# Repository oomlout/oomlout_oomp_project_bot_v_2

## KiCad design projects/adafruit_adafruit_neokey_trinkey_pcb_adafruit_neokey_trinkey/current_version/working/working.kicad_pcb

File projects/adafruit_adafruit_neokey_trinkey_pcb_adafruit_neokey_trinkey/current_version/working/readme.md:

# adafruit_neokey_trinkey_pcb
 
## summary 
* id: adafruit_adafruit_neokey_trinkey_pcb_adafruit_neokey_trinkey
* user: adafruit
* name: adafruit_neokey_trinkey_pcb
* board: adafruit_neokey_trinkey
* repo: https://github.com/adafruit/Adafruit-NeoKey-Trinkey-PCB

* src_file_repo_sch: 
* src_file_repo_sch_link: https://github.com/adafruit/Adafruit-NeoKey-Trinkey-PCB/tree/main/
* full details link: https://github.com/oomlout/oomlout_oomp_project_bot_v_2/tree/main/projects/adafruit_adafruit_neokey_trinkey_pcb_adafruit_neokey_trinkey/current_version/working  

## schematic  
  
[schematic (pdf)](working_schematic.pdf) 

## pcb  

[board (pdf)](working.pdf)  

## working_bom
| Id | Designator | Footprint | Quantity | Designation | Supplier and ref |  | None | 
| --- | --- | --- | --- | --- | --- | --- | --- | 
| 1 | SWD0 | TP15R | 1 | SWD |  |  | [''] | 
| 2 | RESET0 | BTN_KMR2_4.6X2.8 | 1 | KMR2 |  |  | [''] | 
| 3 | U$8 | PCBFEAT-REV-040 | 1 |  |  |  | [''] | 
| 4 | SWC0 | TP15R | 1 | SWC |  |  | [''] | 
| 5 | C8,C3 | 0805-NO | 2 | 10uF |  |  | [''] | 
| 6 | FID2,FID1 | FIDUCIAL_1MM | 2 | FIDUCIAL_1MM |  |  | [''] | 
| 7 | C4,C5 | 0603-NO | 2 | 1uF |  |  | [''] | 
| 8 | IC3 | QFN32_5MM | 1 | ATSAMD21E |  |  | [''] | 
| 9 | U$6 | ADAFRUIT_9MM | 1 |  |  |  | [''] | 
| 10 | RST0 | TP16R | 1 | RST |  |  | [''] | 
| 11 | U1 | SOT23-5 | 1 | AP2112K-3.3 |  |  | [''] | 
| 12 | SW1 | KAILH_BOX_MX_NOSTABILIZERS | 1 | MX |  |  | [''] | 
| 13 | CN1 | USBA_PCB | 1 |  |  |  | [''] | 
| 14 | LED1 | NEO3535_REVERSE | 1 | WS2812B_SK6812E |  |  | [''] | 

## bom_schematic
| Ref | Qnty | Value | Cmp name | Footprint | Description | Vendor | DNP | 
| --- | --- | --- | --- | --- | --- | --- | --- | 
| C3, C8 | 2 | 10uF | CAP_CERAMIC0805-NOOUTLINE | working:0805-NO |  |  |  | 
| C4, C5 | 2 | 1uF | CAP_CERAMIC0603_NO | working:0603-NO |  |  |  | 
| CN1 | 1 | USB_TYPEAPCB | USB_TYPEAPCB | working:USBA_PCB |  |  |  | 
| FID1, FID2 | 2 | FIDUCIAL_1MM | FIDUCIAL_1MM | working:FIDUCIAL_1MM |  |  |  | 
| IC3 | 1 | ATSAMD21E | ATSAMD21E | working:QFN32_5MM |  |  |  | 
| LED1 | 1 | WS2812B_SK6812E | WS2812B_SK6812E | working:NEO3535_REVERSE |  |  |  | 
| RESET0 | 1 | KMR2 | SWITCH_TACT_SMT4.6X2.8 | working:BTN_KMR2_4.6X2.8 |  |  |  | 
| RST0 | 1 | TPTP16R | TPTP16R | working:TP16R |  |  |  | 
| SW1 | 1 | MX | SWITCH_PUSHBUTTON_KAILH_THMSIMPLE | working:KAILH_BOX_MX_NOSTABILIZERS |  |  |  | 
| SWC0 | 1 | TPTP15R | TPTP15R | working:TP15R |  |  |  | 
| SWD0 | 1 | TPTP15R | TPTP15R | working:TP15R |  |  |  | 
| U1 | 1 | AP2112K-3.3 | VREG_SOT23-5 | working:SOT23-5 |  |  |  |

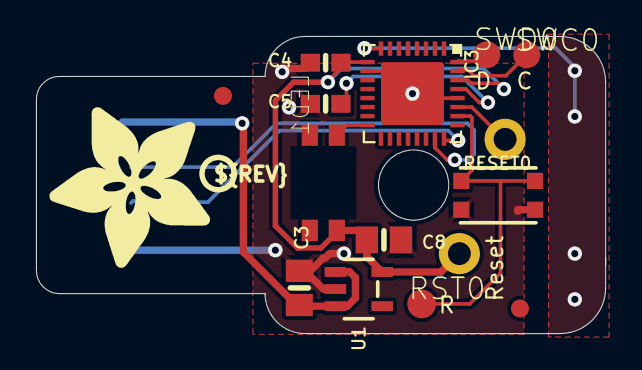
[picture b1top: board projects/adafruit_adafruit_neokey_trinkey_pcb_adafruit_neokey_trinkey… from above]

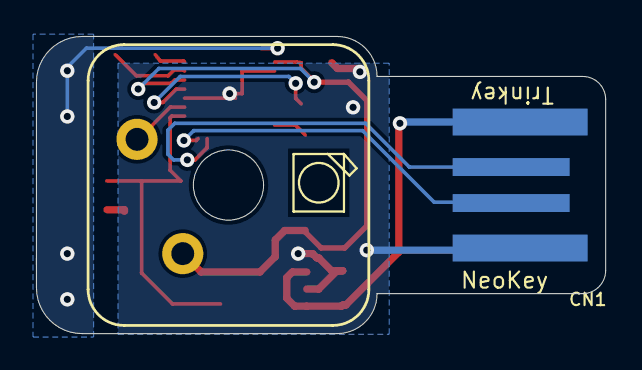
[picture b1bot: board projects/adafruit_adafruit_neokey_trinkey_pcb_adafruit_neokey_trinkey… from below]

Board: 2 copper layers, 31.6 x 16.5 mm, 17 parts (3 on the bottom side), 11 nets.

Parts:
C3, C8: 10uF; 0805-NO
C4, C5: 1uF; 0603-NO
CN1: USBA_PCB
FID1, FID2: FIDUCIAL_1MM
IC3: ATSAMD21E; QFN32_5MM
LED1: WS2812B_SK6812E; NEO3535_REVERSE
RESET0: KMR2; BTN_KMR2_4.6X2.8
RST0: RST; TP16R
SW1: MX; KAILH_BOX_MX_NOSTABILIZERS
SWC0: SWC; TP15R
SWD0: SWD; TP15R
U1: AP2112K-3.3; SOT23-5
U$6: ADAFRUIT_9MM
U$8: PCBFEAT-REV-040

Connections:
3.3V: C4.1, C8.1, IC3.9, IC3.30, LED1.1-VDD, SW1.1, U1.5
D+: CN1.USB_PLUS, IC3.24
D-: CN1.USB_NEG, IC3.23
GND: C3.2, C4.2, C5.2, C8.2, CN1.GND, IC3.10, IC3.28, IC3.33, LED1.3-GND, RESET0.B, RESET0.B', U1.2
unnamed: IC3.16, LED1.4-DIN
SWCLK: IC3.31, SWC0.TP
SWDIO: IC3.32, SWD0.TP
SWITCH: IC3.27, SW1.2
VBUS: C3.1, CN1.VCC, U1.1, U1.3
VDDCORE1: C5.1, IC3.29
~RESET: IC3.26, RESET0.A, RESET0.A', RST0.TP

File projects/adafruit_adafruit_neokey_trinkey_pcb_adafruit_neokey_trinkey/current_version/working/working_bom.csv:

"Id";"Designator";"Footprint";"Quantity";"Designation";"Supplier and ref";
1;"SWD0";"TP15R";1;"SWD";;;
2;"RESET0";"BTN_KMR2_4.6X2.8";1;"KMR2";;;
3;"U$8";"PCBFEAT-REV-040";1;"";;;
4;"SWC0";"TP15R";1;"SWC";;;
5;"C8,C3";"0805-NO";2;"10uF";;;
6;"FID2,FID1";"FIDUCIAL_1MM";2;"FIDUCIAL_1MM";;;
7;"C4,C5";"0603-NO";2;"1uF";;;
8;"IC3";"QFN32_5MM";1;"ATSAMD21E";;;
9;"U$6";"ADAFRUIT_9MM";1;"";;;
10;"RST0";"TP16R";1;"RST";;;
11;"U1";"SOT23-5";1;"AP2112K-3.3";;;
12;"SW1";"KAILH_BOX_MX_NOSTABILIZERS";1;"MX";;;
13;"CN1";"USBA_PCB";1;"";;;
14;"LED1";"NEO3535_REVERSE";1;"WS2812B_SK6812E";;;

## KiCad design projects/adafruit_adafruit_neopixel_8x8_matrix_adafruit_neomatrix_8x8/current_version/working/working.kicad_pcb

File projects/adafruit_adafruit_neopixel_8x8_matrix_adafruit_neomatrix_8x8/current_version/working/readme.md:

# adafruit_neopixel_8x8_matrix
 
## summary 
* id: adafruit_adafruit_neopixel_8x8_matrix_adafruit_neomatrix_8x8
* user: adafruit
* name: adafruit_neopixel_8x8_matrix
* board: adafruit_neomatrix_8x8
* repo: https://github.com/adafruit/Adafruit-NeoPixel-8x8-Matrix

* src_file_repo_sch: 
* src_file_repo_sch_link: https://github.com/adafruit/Adafruit-NeoPixel-8x8-Matrix/tree/master/
* full details link: https://github.com/oomlout/oomlout_oomp_project_bot_v_2/tree/main/projects/adafruit_adafruit_neopixel_8x8_matrix_adafruit_neomatrix_8x8/current_version/working  

## schematic  
  
[schematic (pdf)](working_schematic.pdf) 

## pcb  

[board (pdf)](working.pdf)  

## working_bom
| Id | Designator | Footprint | Quantity | Designation | Supplier and ref |  | None | 
| --- | --- | --- | --- | --- | --- | --- | --- | 
| 1 | C47,C55,C41,C30,C10,C7,C29,C1,C50,C19,C28,C2,C3,C12,C5,C33,C15,R1,C27,C57,C62,C46,C25,C35,C43,C31,C37,C58,C39,C59,C44,C26,C23,C34,C45,C49,C9,C61,C52,C51,C36,C63,C21,C11,C17,C4,C38,C6,C22,C13,C54,C42,C18,C60,C20,C14,C53 | 0805-NO | 57 |  |  |  | [''] | 
| 2 | LED52,LED12,LED31,LED28,LED60,LED62,LED34,LED44,LED1,LED51,LED61,LED14,LED49,LED46,LED2,LED3,LED4,LED43,LED55,LED32,LED17,LED58,LED37,LED63,LED30,LED53,LED18,LED22,LED40,LED45,LED20,LED29,LED15,LED11,LED41,LED8,LED50,LED48,LED57,LED39,LED26,LED13,LED7,LED35,LED38,LED25,LED24,LED23,LED10,LED64,LED9,LED16,LED21,LED54,LED47,LED42,LED56,LED36,LED6,LED27,LED5,LED19,LED59,LED33 | WS2812B | 64 | WS2812B5050 |  |  | [''] | 
| 3 | @HOLE0,@HOLE9,@HOLE1,@HOLE5,@HOLE4,@HOLE10,@HOLE6,@HOLE11,@HOLE2,@HOLE3,@HOLE8,@HOLE7 |  | 12 |  |  |  | [''] | 
| 4 | JP2,JP1 | 1X03 | 2 |  |  |  | [''] | 
| 5 | U$2 | PCBFEAT-REV-040 | 1 |  |  |  | [''] | 
| 6 | FID3,FID2,FID1 | FIDUCIAL_1MM | 3 | FIDUCIAL" |  |  | [''] | 
| 7 | TP11,TP3,TP4,TP14,TP9,TP12,TP1,TP6,TP8,TP10,TP7,TP13,TP2,TP5 | TESTPOINT_SMT | 14 |  |  |  | [''] | 
| 8 | U$1 | ADAFRUIT_TEXT_30MM | 1 |  |  |  | [''] | 

## bom_schematic
| Ref | Qnty | Value | Cmp name | Footprint | Description | Vendor | DNP | 
| --- | --- | --- | --- | --- | --- | --- | --- | 
| C1, C2, C3, C4, C5, C6, C7, C9, C10, C11, C12, C13, C14, C15, C17, C18, C19, C20, C21, C22, C23, C25, C26, C27, C28, C29, C30, C31, C33, C34, C35, C36, C37, C38, C39, C41, C42, C43, C44, C45, C46, C47, C49, C50, C51, C52, C53, C54, C55, C57, C58, C59, C60, C61, C62, C63 | 56 | CAP_CERAMIC0805-NOOUTLINE | CAP_CERAMIC0805-NOOUTLINE | working:0805-NO |  |  |  | 
| FID1, FID2, FID3 | 3 | FIDUCIAL"" | FIDUCIAL{dblquote}{dblquote} | working:FIDUCIAL_1MM |  |  |  | 
| JP1, JP2 | 2 | M03PTH | M03PTH | working:1X03 |  |  |  | 
| LED1, LED2, LED3, LED4, LED5, LED6, LED7, LED8, LED9, LED10, LED11, LED12, LED13, LED14, LED15, LED16, LED17, LED18, LED19, LED20, LED21, LED22, LED23, LED24, LED25, LED26, LED27, LED28, LED29, LED30, LED31, LED32, LED33, LED34, LED35, LED36, LED37, LED38, LED39, LED40, LED41, LED42, LED43, LED44, LED45, LED46, LED47, LED48, LED49, LED50, LED51, LED52, LED53, LED54, LED55, LED56, LED57, LED58, LED59, LED60, LED61, LED62, LED63, LED64 | 64 | WS2812B5050 | WS2812B5050 | working:WS2812B |  |  |  | 
| R1 | 1 | RESISTOR0805_NOOUTLINE | RESISTOR0805_NOOUTLINE | working:0805-NO |  |  |  | 
| TP1, TP2, TP3, TP4, TP5, TP6, TP7, TP8, TP9, TP10, TP11, TP12, TP13, TP14 | 14 | TESTPOINT | TESTPOINT | working:TESTPOINT_SMT |  |  |  |

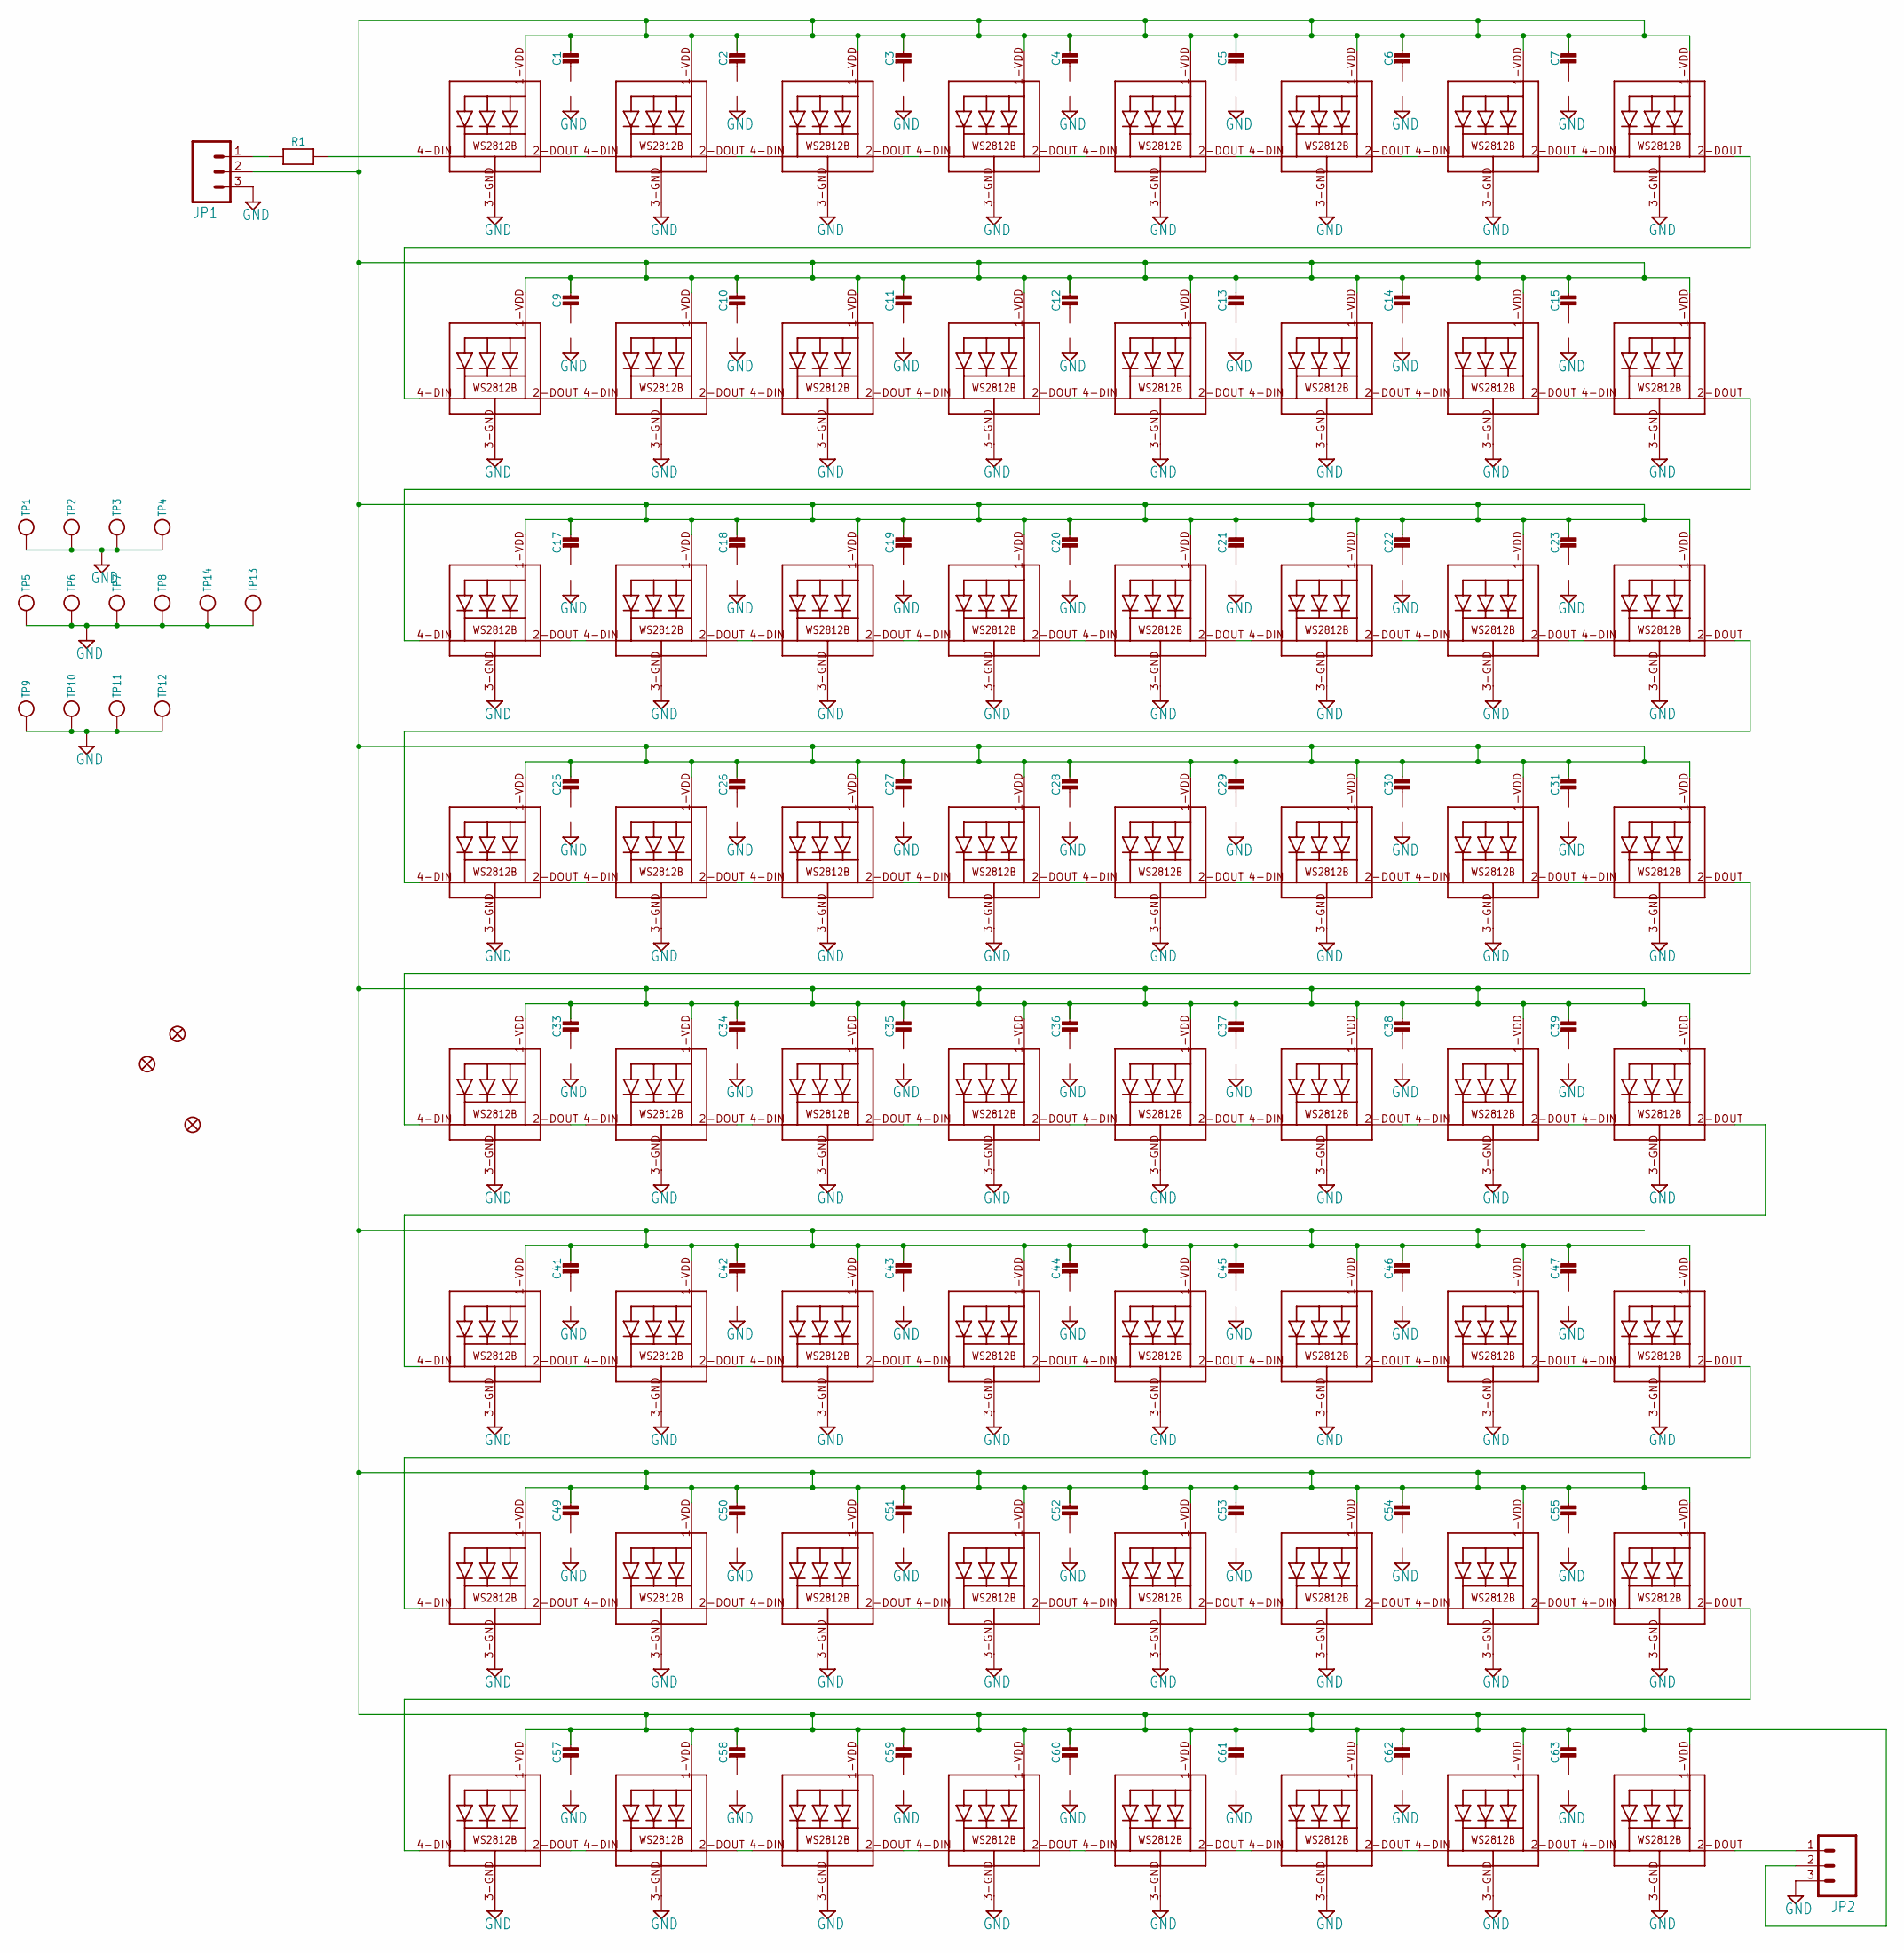
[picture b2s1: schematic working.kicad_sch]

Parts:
C1, C2, C3, C4, C5, C6, C7, C9, C10, C11, C12, C13, C14, C15, C17, C18, C19, C20, C21, C22, C23, C25, C26, C27, C28, C29, C30, C31, C33, C34, C35, C36, C37, C38, C39, C41, C42, C43, C44, C45, C46, C47, C49, C50, C51, C52, C53, C54, C55, C57, C58, C59, C60, C61, C62, C63: CAP_CERAMIC0805-NOOUTLINE; 0805-NO
FID1, FID2, FID3: FIDUCIAL""; FIDUCIAL_1MM
JP1, JP2: M03PTH; 1X03
LED1, LED2, LED3, LED4, LED5, LED6, LED7, LED8, LED9, LED10, LED11, LED12, LED13, LED14, LED15, LED16, LED17, LED18, LED19, LED20, LED21, LED22, LED23, LED24, LED25, LED26, LED27, LED28, LED29, LED30, LED31, LED32, LED33, LED34, LED35, LED36, LED37, LED38, LED39, LED40, LED41, LED42, LED43, LED44, LED45, LED46, LED47, LED48, LED49, LED50, LED51, LED52, LED53, LED54, LED55, LED56, LED57, LED58, LED59, LED60, LED61, LED62, LED63, LED64: WS2812B5050; WS2812B
R1: RESISTOR0805_NOOUTLINE; 0805-NO
TP1, TP2, TP3, TP4, TP5, TP6, TP7, TP8, TP9, TP10, TP11, TP12, TP13, TP14: TESTPOINT; TESTPOINT_SMT

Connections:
GND: C1.2, C2.2, C3.2, C4.2, C5.2, C6.2, C7.2, C9.2, C10.2, C11.2, C12.2, C13.2, C14.2, C15.2, C17.2, C18.2, C19.2, C20.2, C21.2, C22.2, C23.2, C25.2, C26.2, C27.2, C28.2, C29.2, C30.2, C31.2, C33.2, C34.2, C35.2, C36.2, C37.2, C38.2, C39.2, C41.2, C42.2, C43.2, C44.2, C45.2, C46.2, C47.2, C49.2, C50.2, C51.2, C52.2, C53.2, C54.2, C55.2, C57.2, C58.2, C59.2, C60.2, C61.2, C62.2, C63.2, JP1.3, JP2.3, LED1.3-GND (GND), LED2.3-GND (GND), LED3.3-GND (GND), LED4.3-GND (GND), LED5.3-GND (GND), LED6.3-GND (GND), LED7.3-GND (GND), LED8.3-GND (GND), LED9.3-GND (GND), LED10.3-GND (GND), LED11.3-GND (GND), LED12.3-GND (GND), LED13.3-GND (GND), LED14.3-GND (GND), LED15.3-GND (GND), LED16.3-GND (GND), LED17.3-GND (GND), LED18.3-GND (GND), LED19.3-GND (GND), LED20.3-GND (GND), LED21.3-GND (GND), LED22.3-GND (GND)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
unnamed: LED1.4-DIN (DI), R1.2
unnamed: LED8.2-DOUT (DO), LED9.4-DIN (DI)
unnamed: LED16.2-DOUT (DO), LED17.4-DIN (DI)
unnamed: LED24.2-DOUT (DO), LED25.4-DIN (DI)
unnamed: LED40.2-DOUT (DO), LED41.4-DIN (DI)
unnamed: LED32.2-DOUT (DO), LED33.4-DIN (DI)
unnamed: LED48.2-DOUT (DO), LED49.4-DIN (DI)
unnamed: LED56.2-DOUT (DO), LED57.4-DIN (DI)
unnamed: JP2.1, LED64.2-DOUT (DO)
unnamed: JP1.1, R1.1
unnamed: LED17.2-DOUT (DO), LED18.4-DIN (DI)
unnamed: LED25.2-DOUT (DO), LED26.4-DIN (DI)
unnamed: LED26.2-DOUT (DO), LED27.4-DIN (DI)
unnamed: LED2.2-DOUT (DO), LED3.4-DIN (DI)
unnamed: LED3.2-DOUT (DO), LED4.4-DIN (DI)
unnamed: LED4.2-DOUT (DO), LED5.4-DIN (DI)
unnamed: LED5.2-DOUT (DO), LED6.4-DIN (DI)
unnamed: LED6.2-DOUT (DO), LED7.4-DIN (DI)
unnamed: LED7.2-DOUT (DO), LED8.4-DIN (DI)
unnamed: LED10.2-DOUT (DO), LED11.4-DIN (DI)
unnamed: LED11.2-DOUT (DO), LED12.4-DIN (DI)
unnamed: LED12.2-DOUT (DO), LED13.4-DIN (DI)
unnamed: LED13.2-DOUT (DO), LED14.4-DIN (DI)
unnamed: LED14.2-DOUT (DO), LED15.4-DIN (DI)
unnamed: LED15.2-DOUT (DO), LED16.4-DIN (DI)
unnamed: LED18.2-DOUT (DO), LED19.4-DIN (DI)
unnamed: LED19.2-DOUT (DO), LED20.4-DIN (DI)
unnamed: LED20.2-DOUT (DO), LED21.4-DIN (DI)
unnamed: LED21.2-DOUT (DO), LED22.4-DIN (DI)
unnamed: LED22.2-DOUT (DO), LED23.4-DIN (DI)
unnamed: LED23.2-DOUT (DO), LED24.4-DIN (DI)
unnamed: LED27.2-DOUT (DO), LED28.4-DIN (DI)
unnamed: LED28.2-DOUT (DO), LED29.4-DIN (DI)
unnamed: LED29.2-DOUT (DO), LED30.4-DIN (DI)
unnamed: LED30.2-DOUT (DO), LED31.4-DIN (DI)
unnamed: LED31.2-DOUT (DO), LED32.4-DIN (DI)
unnamed: LED1.2-DOUT (DO), LED2.4-DIN (DI)
unnamed: LED9.2-DOUT (DO), LED10.4-DIN (DI)
unnamed: LED49.2-DOUT (DO), LED50.4-DIN (DI)
unnamed: LED57.2-DOUT (DO), LED58.4-DIN (DI)
unnamed: LED58.2-DOUT (DO), LED59.4-DIN (DI)
unnamed: LED34.2-DOUT (DO), LED35.4-DIN (DI)
unnamed: LED35.2-DOUT (DO), LED36.4-DIN (DI)
unnamed: LED36.2-DOUT (DO), LED37.4-DIN (DI)
unnamed: LED37.2-DOUT (DO), LED38.4-DIN (DI)
unnamed: LED38.2-DOUT (DO), LED39.4-DIN (DI)
unnamed: LED39.2-DOUT (DO), LED40.4-DIN (DI)
unnamed: LED42.2-DOUT (DO), LED43.4-DIN (DI)
unnamed: LED43.2-DOUT (DO), LED44.4-DIN (DI)
unnamed: LED44.2-DOUT (DO), LED45.4-DIN (DI)
unnamed: LED45.2-DOUT (DO), LED46.4-DIN (DI)
unnamed: LED46.2-DOUT (DO), LED47.4-DIN (DI)
unnamed: LED47.2-DOUT (DO), LED48.4-DIN (DI)
unnamed: LED50.2-DOUT (DO), LED51.4-DIN (DI)
unnamed: LED51.2-DOUT (DO), LED52.4-DIN (DI)
unnamed: LED52.2-DOUT (DO), LED53.4-DIN (DI)
unnamed: LED53.2-DOUT (DO), LED54.4-DIN (DI)
unnamed: LED54.2-DOUT (DO), LED55.4-DIN (DI)
unnamed: LED55.2-DOUT (DO), LED56.4-DIN (DI)
unnamed: LED59.2-DOUT (DO), LED60.4-DIN (DI)
unnamed: LED60.2-DOUT (DO), LED61.4-DIN (DI)
unnamed: LED61.2-DOUT (DO), LED62.4-DIN (DI)
unnamed: LED62.2-DOUT (DO), LED63.4-DIN (DI)
unnamed: LED63.2-DOUT (DO), LED64.4-DIN (DI)
unnamed: LED33.2-DOUT (DO), LED34.4-DIN (DI)
unnamed: LED41.2-DOUT (DO), LED42.4-DIN (DI)
VDD: C1.1, C2.1, C3.1, C4.1, C5.1, C6.1, C7.1, C9.1, C10.1, C11.1, C12.1, C13.1, C14.1, C15.1, C17.1, C18.1, C19.1, C20.1, C21.1, C22.1, C23.1, C25.1, C26.1, C27.1, C28.1, C29.1, C30.1, C31.1, C33.1, C34.1, C35.1, C36.1, C37.1, C38.1, C39.1, C41.1, C42.1, C43.1, C44.1, C45.1, C46.1, C47.1, C49.1, C50.1, C51.1, C52.1, C53.1, C54.1, C55.1, C57.1, C58.1, C59.1, C60.1, C61.1, C62.1, C63.1, JP1.2, JP2.2, LED1.1-VDD (VDD), LED2.1-VDD (VDD), LED3.1-VDD (VDD), LED4.1-VDD (VDD), LED5.1-VDD (VDD), LED6.1-VDD (VDD), LED7.1-VDD (VDD), LED8.1-VDD (VDD), LED9.1-VDD (VDD), LED10.1-VDD (VDD), LED11.1-VDD (VDD), LED12.1-VDD (VDD), LED13.1-VDD (VDD), LED14.1-VDD (VDD), LED15.1-VDD (VDD), LED16.1-VDD (VDD), LED17.1-VDD (VDD), LED18.1-VDD (VDD), LED19.1-VDD (VDD), LED20.1-VDD (VDD), LED21.1-VDD (VDD), LED22.1-VDD (VDD)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

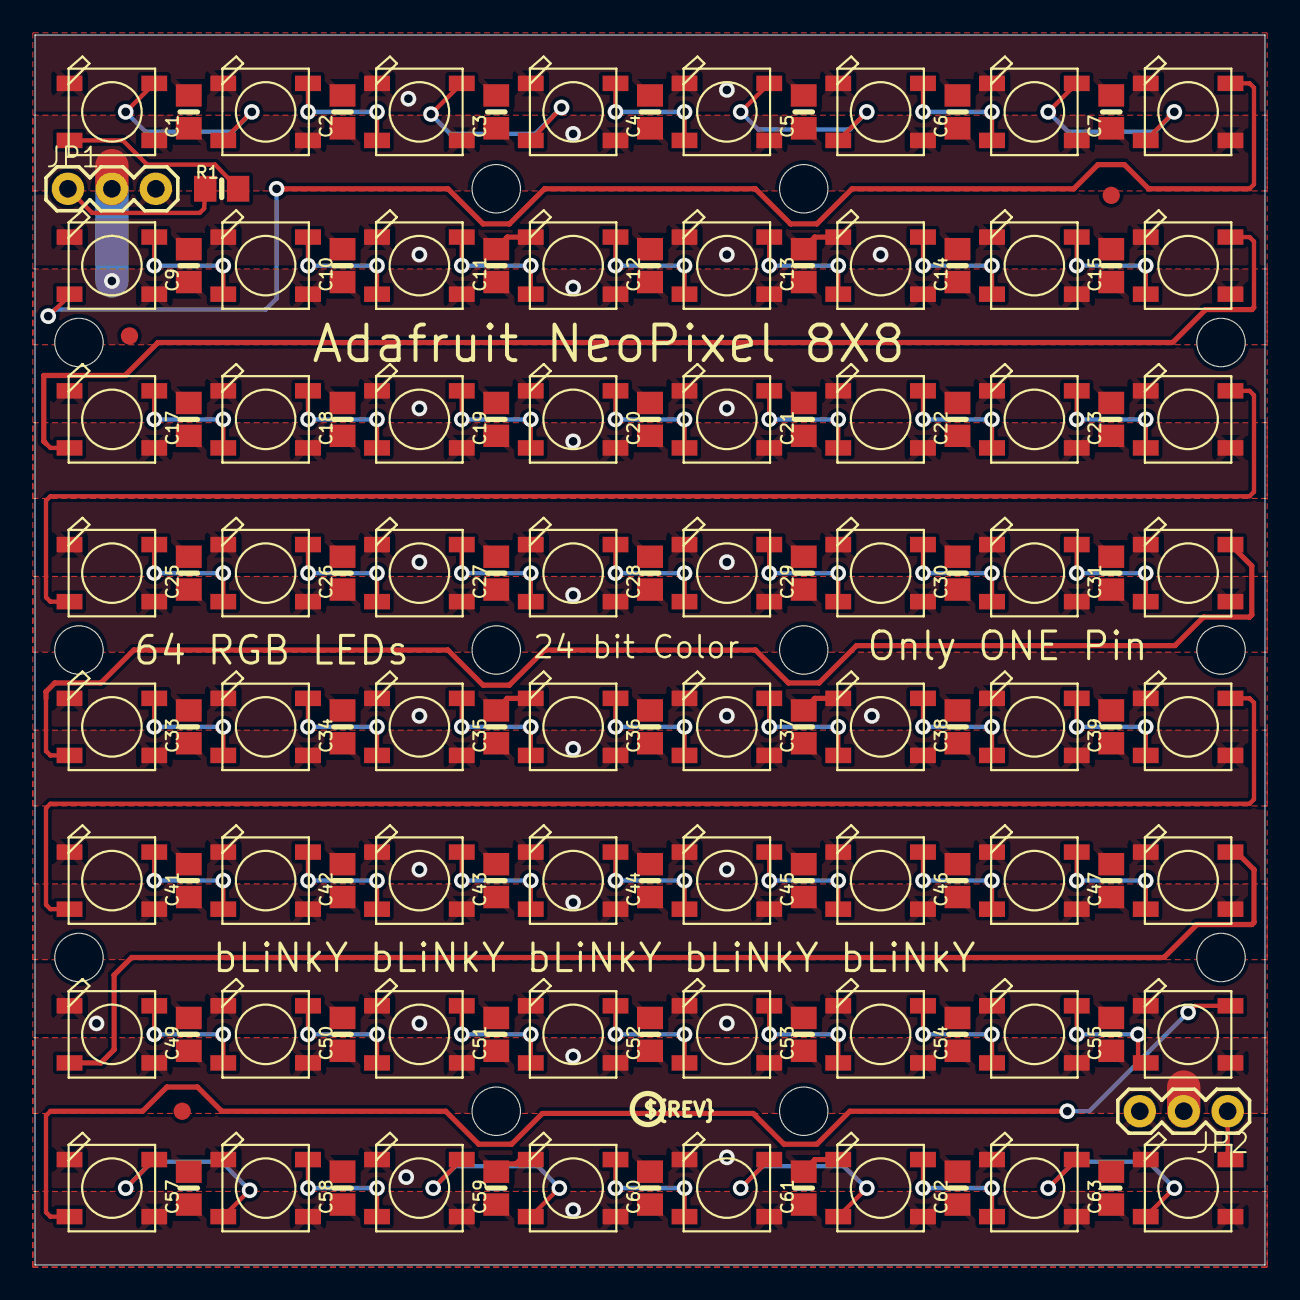
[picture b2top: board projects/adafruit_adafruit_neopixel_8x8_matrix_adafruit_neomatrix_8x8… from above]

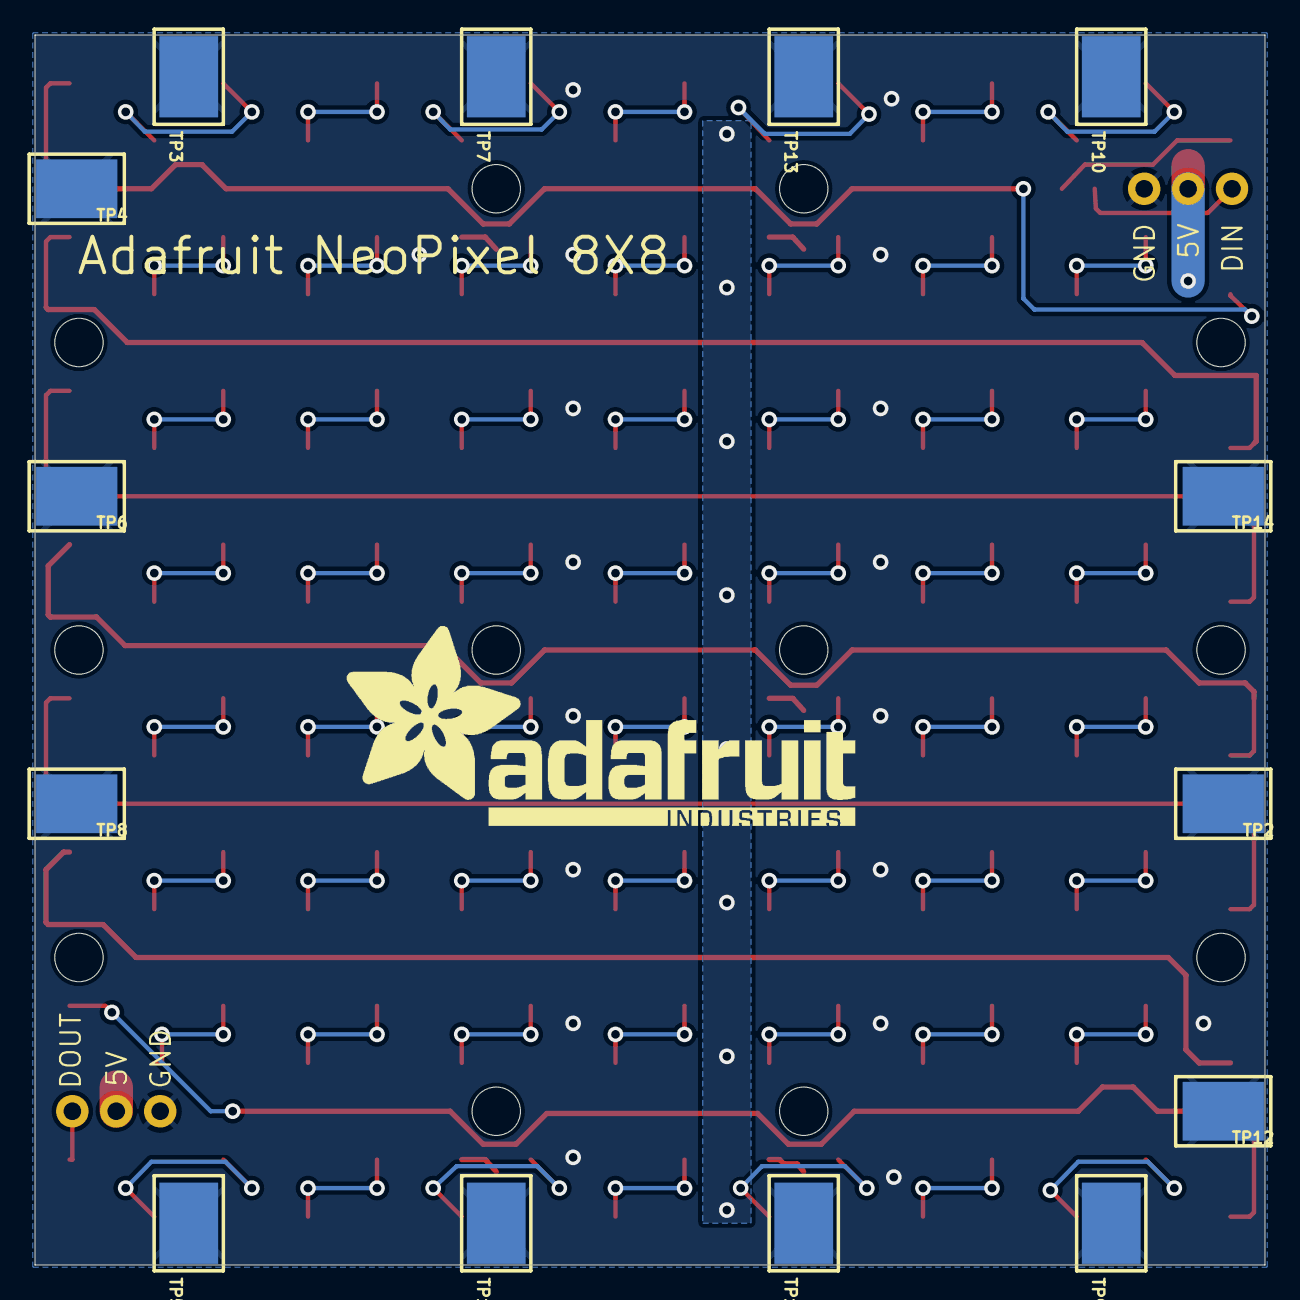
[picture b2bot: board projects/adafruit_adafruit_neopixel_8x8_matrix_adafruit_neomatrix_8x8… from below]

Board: 2 copper layers, 71.1 x 71.1 mm, 154 parts (15 on the bottom side), 68 nets.

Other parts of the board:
@HOLE0, @HOLE1, @HOLE2, @HOLE3, @HOLE4, @HOLE5, @HOLE6, @HOLE7, @HOLE8, @HOLE9, @HOLE10, @HOLE11: (no value)
U$1: ADAFRUIT_TEXT_30MM
U$2: PCBFEAT-REV-040

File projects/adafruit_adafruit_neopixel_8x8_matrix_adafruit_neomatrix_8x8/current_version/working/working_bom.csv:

"Id";"Designator";"Footprint";"Quantity";"Designation";"Supplier and ref";
1;"C47,C55,C41,C30,C10,C7,C29,C1,C50,C19,C28,C2,C3,C12,C5,C33,C15,R1,C27,C57,C62,C46,C25,C35,C43,C31,C37,C58,C39,C59,C44,C26,C23,C34,C45,C49,C9,C61,C52,C51,C36,C63,C21,C11,C17,C4,C38,C6,C22,C13,C54,C42,C18,C60,C20,C14,C53";"0805-NO";57;"";;;
2;"LED52,LED12,LED31,LED28,LED60,LED62,LED34,LED44,LED1,LED51,LED61,LED14,LED49,LED46,LED2,LED3,LED4,LED43,LED55,LED32,LED17,LED58,LED37,LED63,LED30,LED53,LED18,LED22,LED40,LED45,LED20,LED29,LED15,LED11,LED41,LED8,LED50,LED48,LED57,LED39,LED26,LED13,LED7,LED35,LED38,LED25,LED24,LED23,LED10,LED64,LED9,LED16,LED21,LED54,LED47,LED42,LED56,LED36,LED6,LED27,LED5,LED19,LED59,LED33";"WS2812B";64;"WS2812B5050";;;
3;"@HOLE0,@HOLE9,@HOLE1,@HOLE5,@HOLE4,@HOLE10,@HOLE6,@HOLE11,@HOLE2,@HOLE3,@HOLE8,@HOLE7";"";12;"";;;
4;"JP2,JP1";"1X03";2;"";;;
5;"U$2";"PCBFEAT-REV-040";1;"";;;
6;"FID3,FID2,FID1";"FIDUCIAL_1MM";3;"FIDUCIAL""";;;
7;"TP11,TP3,TP4,TP14,TP9,TP12,TP1,TP6,TP8,TP10,TP7,TP13,TP2,TP5";"TESTPOINT_SMT";14;"";;;
8;"U$1";"ADAFRUIT_TEXT_30MM";1;"";;;

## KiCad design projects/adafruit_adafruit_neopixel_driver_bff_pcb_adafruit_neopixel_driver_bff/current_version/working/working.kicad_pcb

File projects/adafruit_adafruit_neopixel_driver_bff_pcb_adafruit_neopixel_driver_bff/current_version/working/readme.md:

# adafruit_neopixel_driver_bff_pcb
 
## summary 
* id: adafruit_adafruit_neopixel_driver_bff_pcb_adafruit_neopixel_driver_bff
* user: adafruit
* name: adafruit_neopixel_driver_bff_pcb
* board: adafruit_neopixel_driver_bff
* repo: https://github.com/adafruit/Adafruit-NeoPixel-Driver-BFF-PCB

* src_file_repo_sch: 
* src_file_repo_sch_link: https://github.com/adafruit/Adafruit-NeoPixel-Driver-BFF-PCB/tree/main/
* full details link: https://github.com/oomlout/oomlout_oomp_project_bot_v_2/tree/main/projects/adafruit_adafruit_neopixel_driver_bff_pcb_adafruit_neopixel_driver_bff/current_version/working  

## schematic  
  
[schematic (pdf)](working_schematic.pdf) 

## pcb  

[board (pdf)](working.pdf)  

## working_bom
| Id | Designator | Footprint | Quantity | Designation | Supplier and ref |  | None | 
| --- | --- | --- | --- | --- | --- | --- | --- | 
| 1 | PLABEL12 | PLABEL12 | 1 |  |  |  | [''] | 
| 2 | SJ6,SJ5,SJ2,SJ4,SJ3 | SOLDERJUMPER_ARROW_NOPASTE | 5 |  |  |  | [''] | 
| 3 | PLABEL0 | PLABEL0 | 1 |  |  |  | [''] | 
| 4 | U$8,U$6 | FIDUCIAL_1MM | 2 | FIDUCIAL_1MM |  |  | [''] | 
| 5 | PLABEL7 | PLABEL7 | 1 |  |  |  | [''] | 
| 6 | C4 | 0603-NO | 1 | 1uF |  |  | [''] | 
| 7 | PLABEL14 | PLABEL14 | 1 |  |  |  | [''] | 
| 8 | PLABEL15 | PLABEL15 | 1 |  |  |  | [''] | 
| 9 | IC2 | SOT23-5 | 1 | 74AHCT1G125DBV |  |  | [''] | 
| 10 | PLABEL17 | PLABEL17 | 1 |  |  |  | [''] | 
| 11 | SJ1 | SOLDERJUMPER_CLOSEDWIRE | 1 |  |  |  | [''] | 
| 12 | NEO0 | JSTPH3 | 1 | JST PH 3 |  |  | [''] | 
| 13 | JP2 | 1X01_ROUND_76MIL | 1 |  |  |  | [''] | 
| 14 | PLABEL9 | PLABEL9 | 1 |  |  |  | [''] | 
| 15 | PLABEL2 | PLABEL2 | 1 |  |  |  | [''] | 
| 16 | C3 | 0805-NO | 1 | 10uF |  |  | [''] | 
| 17 | PLABEL16 | PLABEL16 | 1 |  |  |  | [''] | 
| 18 | PLABEL3 | PLABEL3 | 1 |  |  |  | [''] | 
| 19 | PLABEL10 | PLABEL10 | 1 |  |  |  | [''] | 
| 20 | PLABEL8 | PLABEL8 | 1 |  |  |  | [''] | 
| 21 | PLABEL13 | PLABEL13 | 1 |  |  |  | [''] | 
| 22 | R1 | 0603-NO | 1 | 100 |  |  | [''] | 
| 23 | PLABEL6 | PLABEL6 | 1 |  |  |  | [''] | 
| 24 | PLABEL18 | PLABEL18 | 1 |  |  |  | [''] | 
| 25 | PLABEL11 | PLABEL11 | 1 |  |  |  | [''] | 
| 26 | PLABEL5 | PLABEL5 | 1 |  |  |  | [''] | 
| 27 | PLABEL4 | PLABEL4 | 1 |  |  |  | [''] | 
| 28 | PLABEL1 | PLABEL1 | 1 |  |  |  | [''] | 
| 29 | U$2 | ADAFRUIT_3.5MM | 1 |  |  |  | [''] | 
| 30 | PLABEL19 | PLABEL19 | 1 |  |  |  | [''] | 
| 31 | U$3 | PCBFEAT-REV-040 | 1 |  |  |  | [''] | 
| 32 | JP3,JP1 | 1X07_CASTEL | 2 |  |  |  | [''] | 
| 33 | PLABEL20 | PLABEL20 | 1 |  |  |  | [''] | 

## bom_schematic
| Ref | Qnty | Value | Cmp name | Footprint | Description | Vendor | DNP | 
| --- | --- | --- | --- | --- | --- | --- | --- | 
| C3 | 1 | 10uF | CAP_CERAMIC0805-NOOUTLINE | working:0805-NO |  |  |  | 
| C4 | 1 | 1uF | CAP_CERAMIC0603_NO | working:0603-NO |  |  |  | 
| IC2 | 1 | 741G125DBV | 741G125DBV | working:SOT23-5 |  |  |  | 
| JP1, JP3 | 2 | HEADER-1X7_CASTEL | HEADER-1X7_CASTEL | working:1X07_CASTEL |  |  |  | 
| JP2 | 1 | HEADER-1X1ROUND_76MIL | HEADER-1X1ROUND_76MIL | working:1X01_ROUND_76MIL |  |  |  | 
| NEO0 | 1 | JST PH 3 | CON_JST_PH_3PIN | working:JSTPH3 |  |  |  | 
| R1 | 1 | 100 | RESISTOR_0603_NOOUT | working:0603-NO |  |  |  | 
| SJ1 | 1 | SOLDERJUMPERCLOSED | SOLDERJUMPERCLOSED | working:SOLDERJUMPER_CLOSEDWIRE |  |  |  | 
| SJ2, SJ3, SJ4, SJ5, SJ6 | 5 | SOLDERJUMPER | SOLDERJUMPER | working:SOLDERJUMPER_ARROW_NOPASTE |  |  |  | 
| U$6, U$8 | 2 | FIDUCIAL_1MM | FIDUCIAL_1MM | working:FIDUCIAL_1MM |  |  |  |

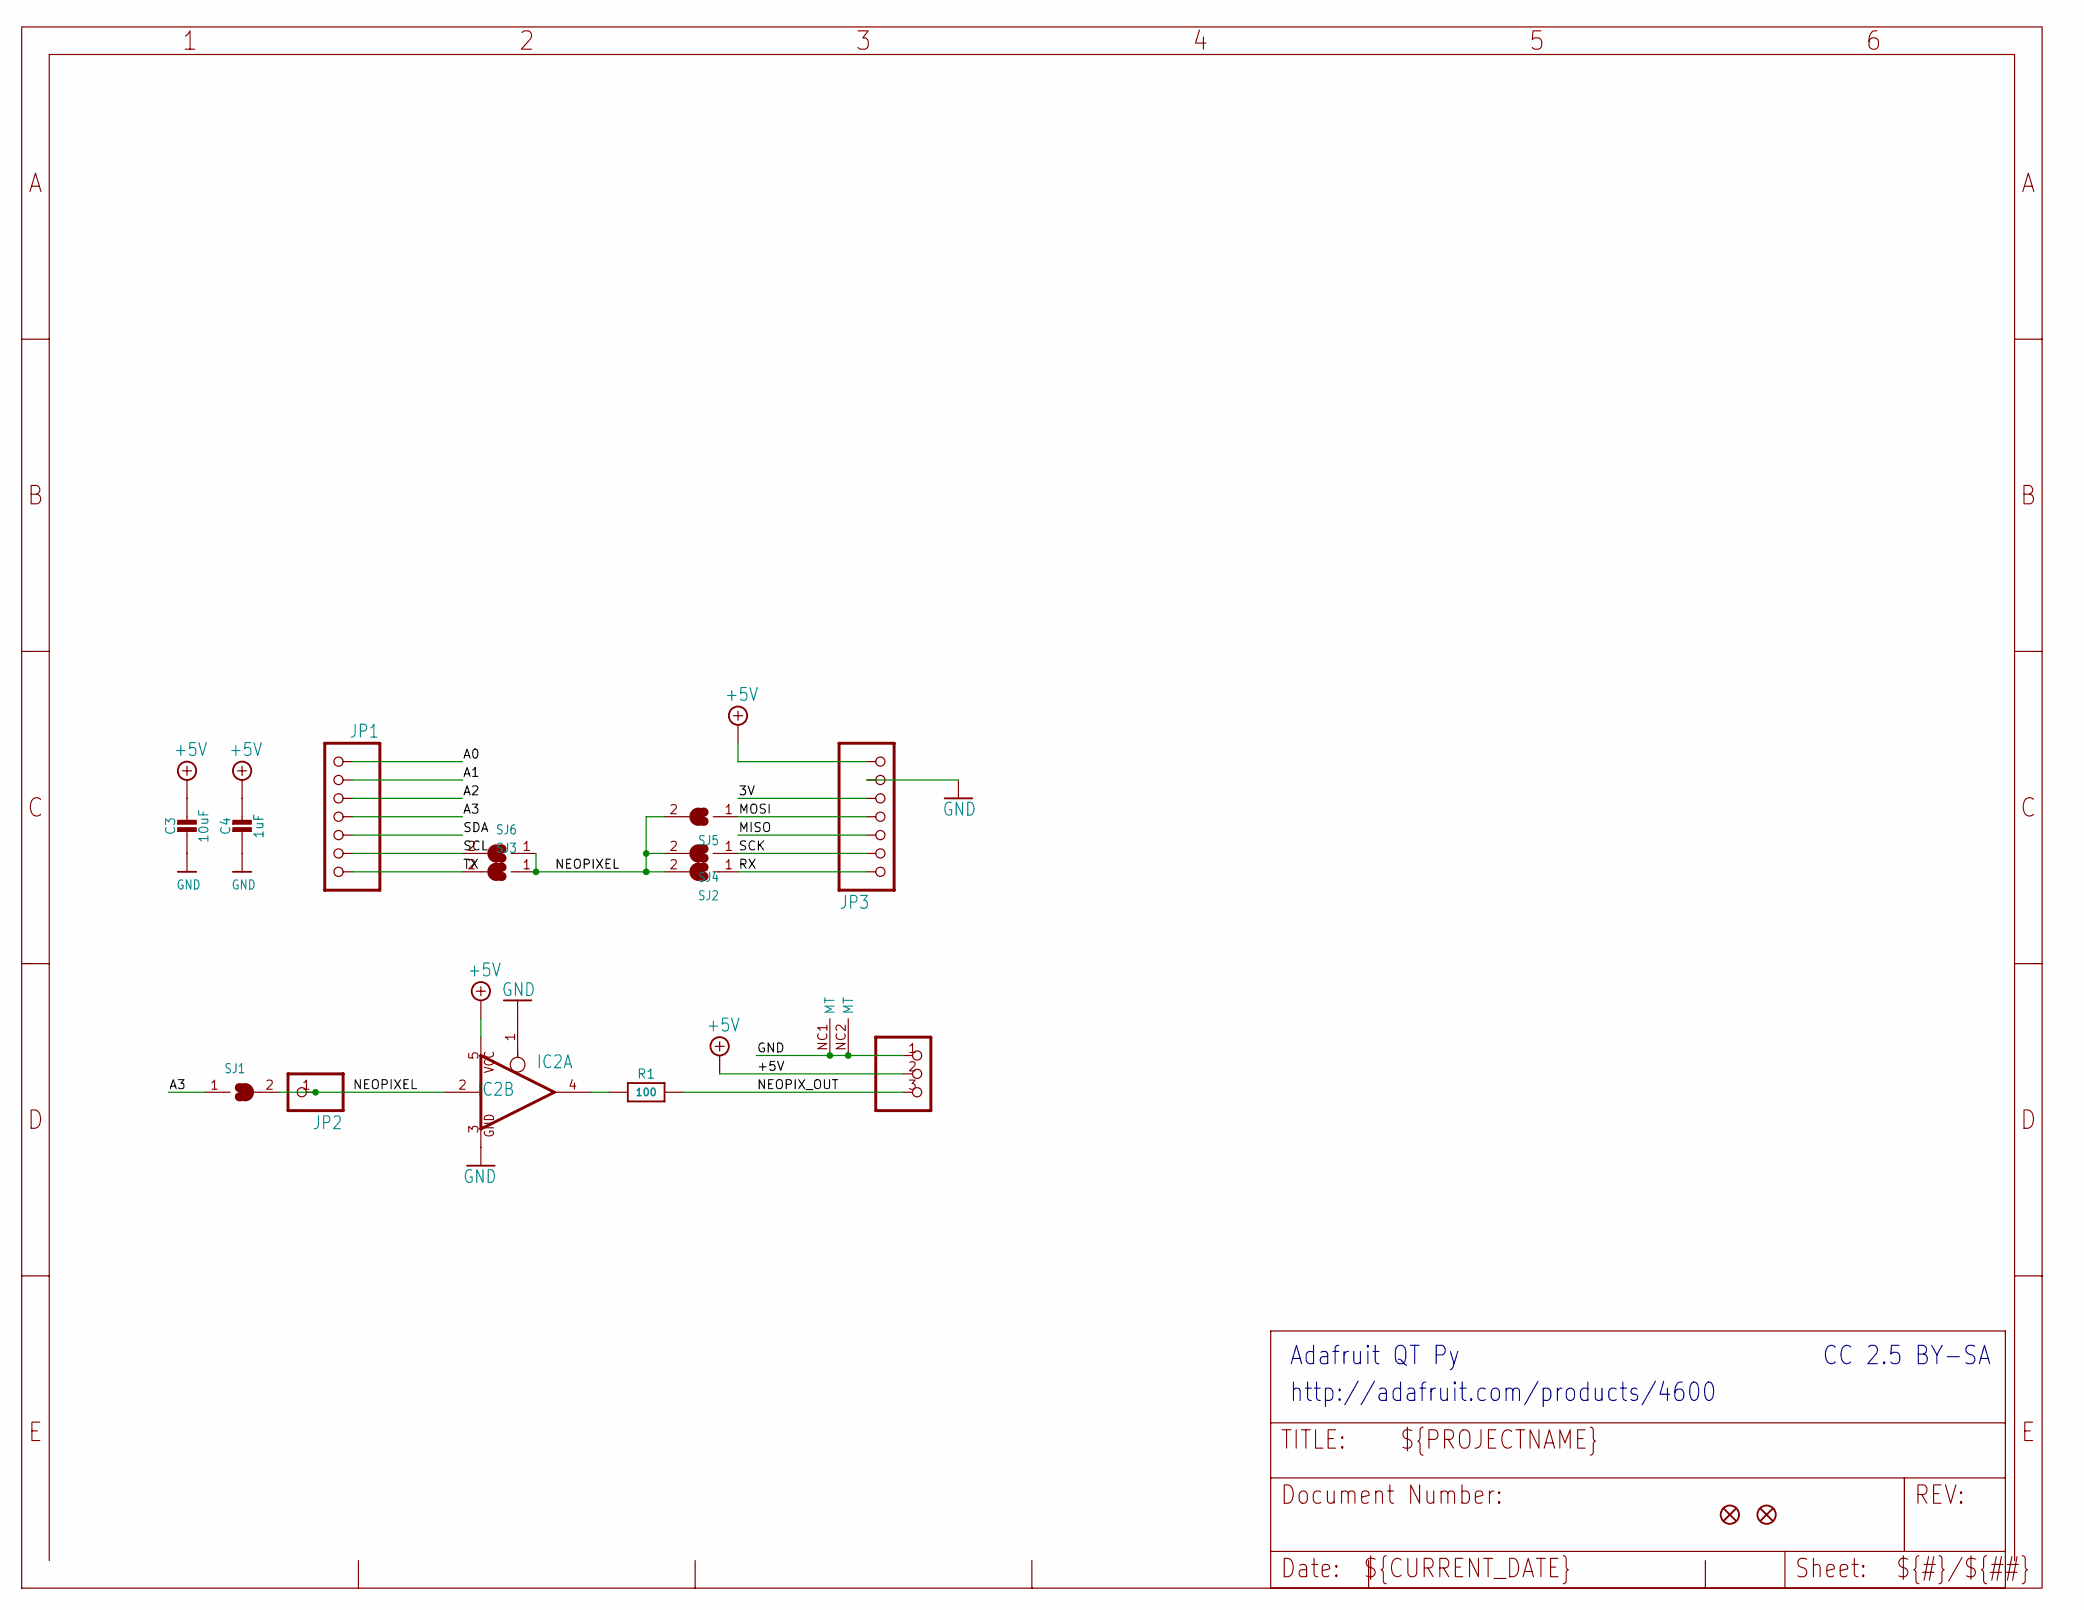
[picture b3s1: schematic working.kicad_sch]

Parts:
C3: 10uF; 0805-NO
C4: 1uF; 0603-NO
IC2: 741G125DBV; SOT23-5
JP1, JP3: HEADER-1X7_CASTEL; 1X07_CASTEL
JP2: HEADER-1X1ROUND_76MIL; 1X01_ROUND_76MIL
NEO0: JST PH 3; JSTPH3
R1: 100; 0603-NO
SJ1: SOLDERJUMPERCLOSED; SOLDERJUMPER_CLOSEDWIRE
SJ2, SJ3, SJ4, SJ5, SJ6: SOLDERJUMPER; SOLDERJUMPER_ARROW_NOPASTE
U$6, U$8: FIDUCIAL_1MM

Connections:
3V: JP3.5, JP3.5C (5)
+5V: C3.1, C4.1, IC2.5 (VCC), JP3.7, JP3.7C (7), NEO0.2
A0: JP1.1, JP1.1C (1)
A1: JP1.2, JP1.2C (2)
A2: JP1.3, JP1.3C (3)
A3: JP1.4, JP1.4C (4), SJ1.1
GND: C3.2, C4.2, IC2.1 (OE), IC2.3 (GND), JP3.6, JP3.6C (6), NEO0.1, NEO0.NC1 (MT), NEO0.NC2 (MT)
MISO: JP3.3, JP3.3C (3)
MOSI: JP3.4, JP3.4C (4), SJ5.1
unnamed: IC2.4 (O), R1.1
NEOPIXEL: IC2.2 (I), JP2.1, SJ1.2, SJ2.2, SJ3.1, SJ4.2, SJ5.2, SJ6.1
NEOPIX_OUT: NEO0.3, R1.2
RX: JP3.1, JP3.1C (1), SJ2.1
SCK: JP3.2, JP3.2C (2), SJ4.1
SCL: JP1.6, JP1.6C (6), SJ6.2
SDA: JP1.5, JP1.5C (5)
TX: JP1.7, JP1.7C (7), SJ3.2

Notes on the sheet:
Adafruit QT Py
CC 2.5 BY-SA
http://adafruit.com/products/4600

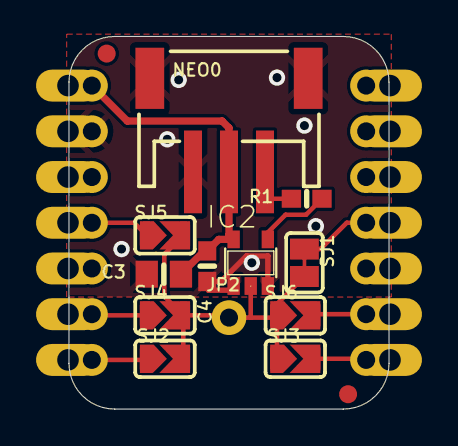
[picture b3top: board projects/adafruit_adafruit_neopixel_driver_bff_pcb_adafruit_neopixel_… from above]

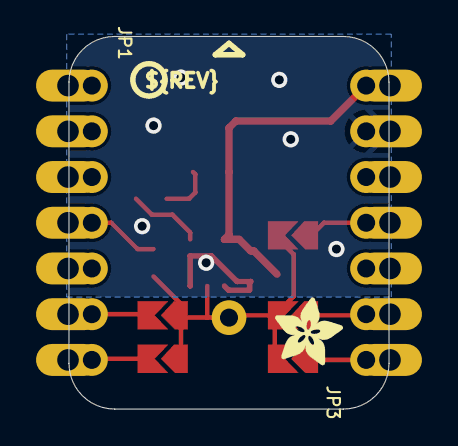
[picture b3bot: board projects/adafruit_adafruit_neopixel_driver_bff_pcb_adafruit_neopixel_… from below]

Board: 16 copper layers, 17.8 x 20.7 mm, 39 parts (6 on the bottom side), 17 nets.

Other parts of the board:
PLABEL0: PLABEL0
PLABEL1: PLABEL1
PLABEL2: PLABEL2
PLABEL3: PLABEL3
PLABEL4: PLABEL4
PLABEL5: PLABEL5
PLABEL6: PLABEL6
PLABEL7: PLABEL7
PLABEL8: PLABEL8
PLABEL9: PLABEL9
PLABEL10: PLABEL10
PLABEL11: PLABEL11
PLABEL12: PLABEL12
PLABEL13: PLABEL13
PLABEL14: PLABEL14
PLABEL15: PLABEL15
PLABEL16: PLABEL16
PLABEL17: PLABEL17
PLABEL18: PLABEL18
PLABEL19: PLABEL19
PLABEL20: PLABEL20
U$2: ADAFRUIT_3.5MM
U$3: PCBFEAT-REV-040

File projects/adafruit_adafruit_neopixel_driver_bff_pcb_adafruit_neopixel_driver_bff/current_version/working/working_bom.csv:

"Id";"Designator";"Footprint";"Quantity";"Designation";"Supplier and ref";
1;"PLABEL12";"PLABEL12";1;"";;;
2;"SJ6,SJ5,SJ2,SJ4,SJ3";"SOLDERJUMPER_ARROW_NOPASTE";5;"";;;
3;"PLABEL0";"PLABEL0";1;"";;;
4;"U$8,U$6";"FIDUCIAL_1MM";2;"FIDUCIAL_1MM";;;
5;"PLABEL7";"PLABEL7";1;"";;;
6;"C4";"0603-NO";1;"1uF";;;
7;"PLABEL14";"PLABEL14";1;"";;;
8;"PLABEL15";"PLABEL15";1;"";;;
9;"IC2";"SOT23-5";1;"74AHCT1G125DBV";;;
10;"PLABEL17";"PLABEL17";1;"";;;
11;"SJ1";"SOLDERJUMPER_CLOSEDWIRE";1;"";;;
12;"NEO0";"JSTPH3";1;"JST PH 3";;;
13;"JP2";"1X01_ROUND_76MIL";1;"";;;
14;"PLABEL9";"PLABEL9";1;"";;;
15;"PLABEL2";"PLABEL2";1;"";;;
16;"C3";"0805-NO";1;"10uF";;;
17;"PLABEL16";"PLABEL16";1;"";;;
18;"PLABEL3";"PLABEL3";1;"";;;
19;"PLABEL10";"PLABEL10";1;"";;;
20;"PLABEL8";"PLABEL8";1;"";;;
21;"PLABEL13";"PLABEL13";1;"";;;
22;"R1";"0603-NO";1;"100";;;
23;"PLABEL6";"PLABEL6";1;"";;;
24;"PLABEL18";"PLABEL18";1;"";;;
25;"PLABEL11";"PLABEL11";1;"";;;
26;"PLABEL5";"PLABEL5";1;"";;;
27;"PLABEL4";"PLABEL4";1;"";;;
28;"PLABEL1";"PLABEL1";1;"";;;
29;"U$2";"ADAFRUIT_3.5MM";1;"";;;
30;"PLABEL19";"PLABEL19";1;"";;;
31;"U$3";"PCBFEAT-REV-040";1;"";;;
32;"JP3,JP1";"1X07_CASTEL";2;"";;;
33;"PLABEL20";"PLABEL20";1;"";;;
